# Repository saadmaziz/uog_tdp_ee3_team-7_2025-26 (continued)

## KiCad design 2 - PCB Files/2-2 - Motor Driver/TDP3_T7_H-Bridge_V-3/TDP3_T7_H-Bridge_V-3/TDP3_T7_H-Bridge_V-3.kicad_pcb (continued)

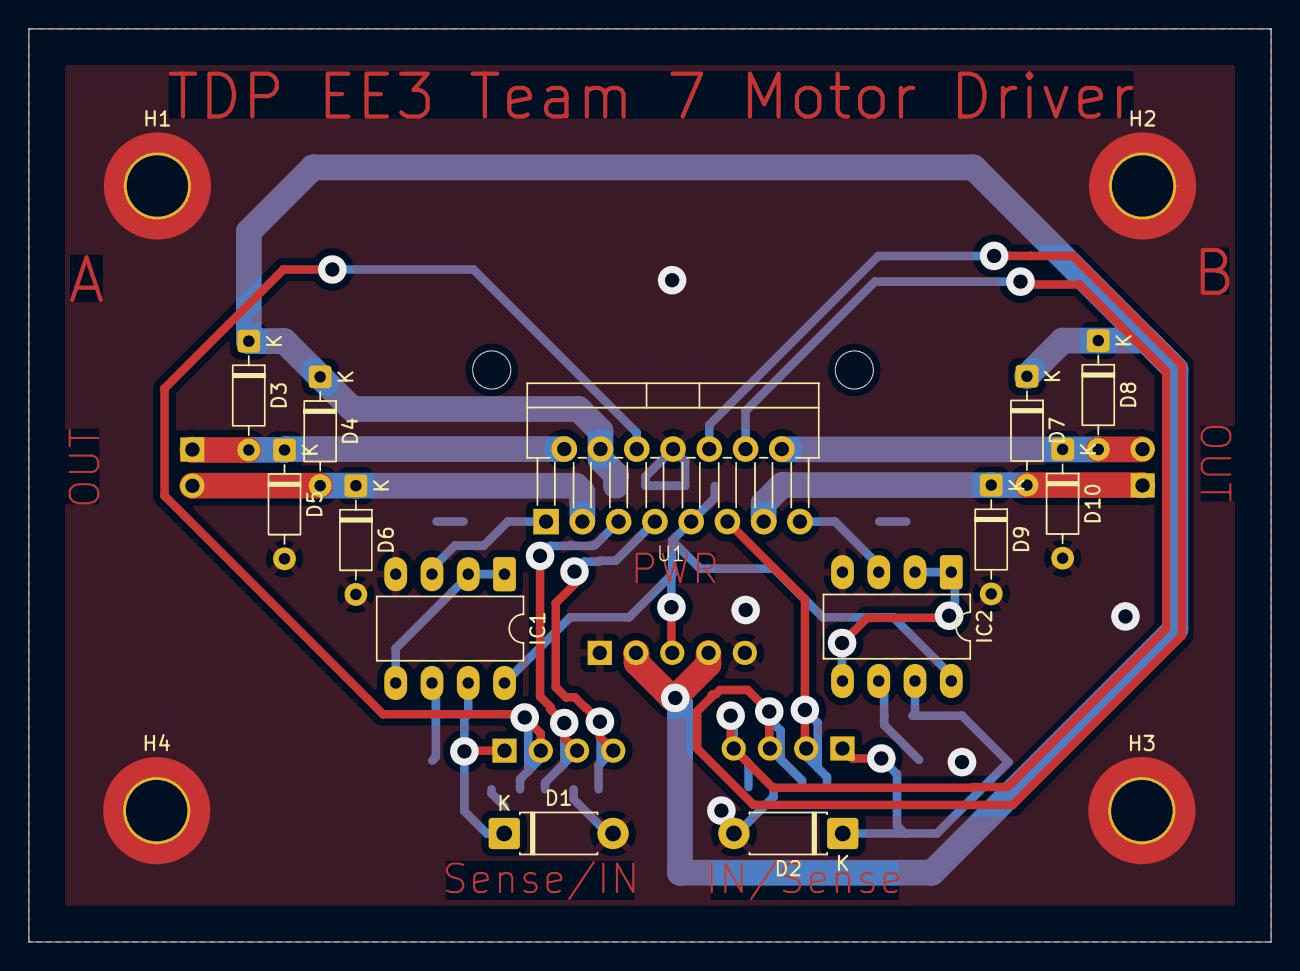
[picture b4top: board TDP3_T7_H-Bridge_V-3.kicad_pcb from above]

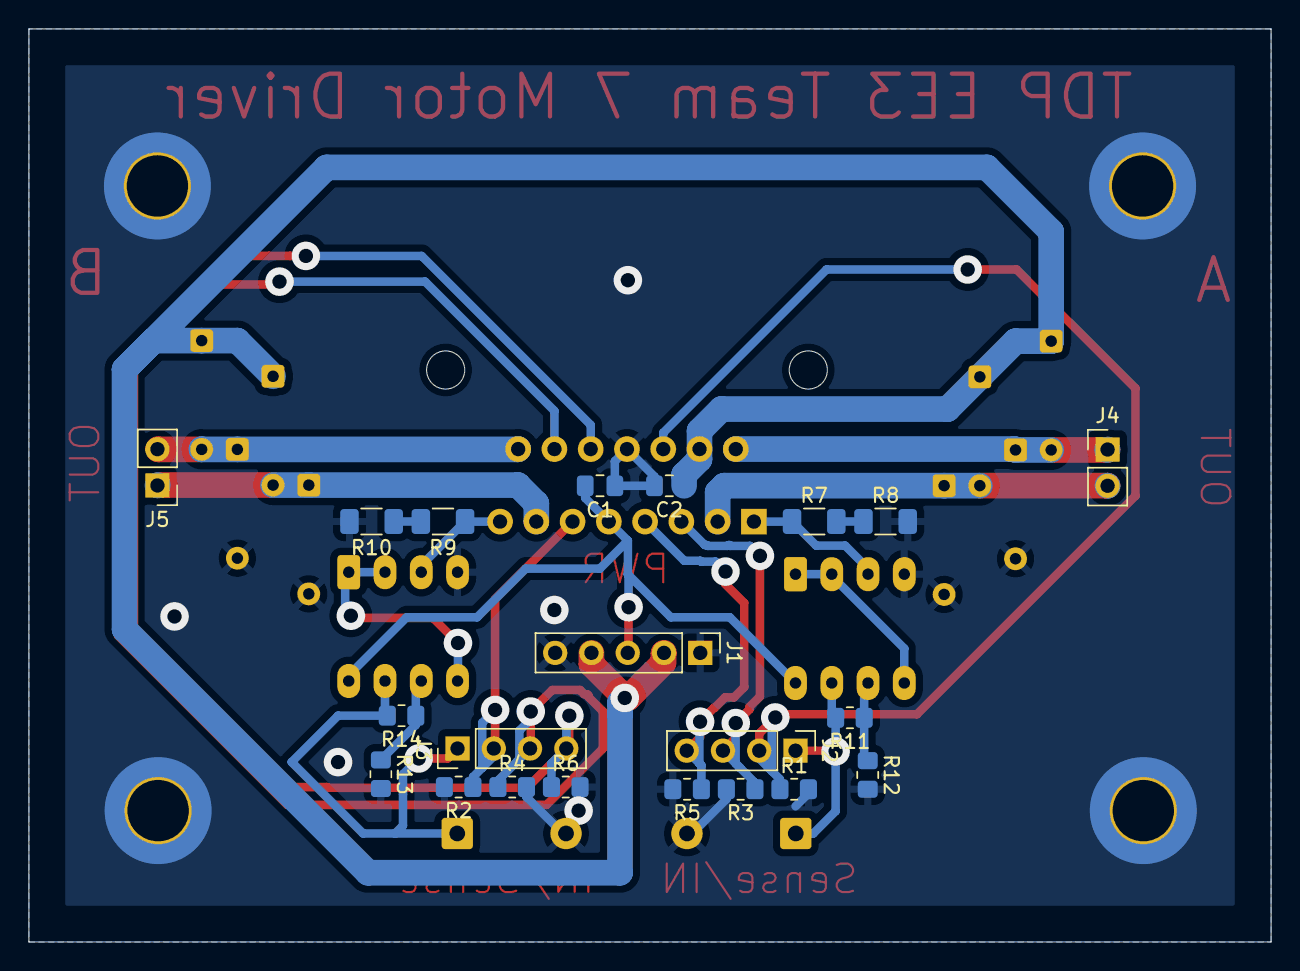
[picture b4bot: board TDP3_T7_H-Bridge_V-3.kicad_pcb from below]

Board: 2 copper layers, 87.0 x 64.0 mm, 38 parts (21 on the bottom side), 23 nets.

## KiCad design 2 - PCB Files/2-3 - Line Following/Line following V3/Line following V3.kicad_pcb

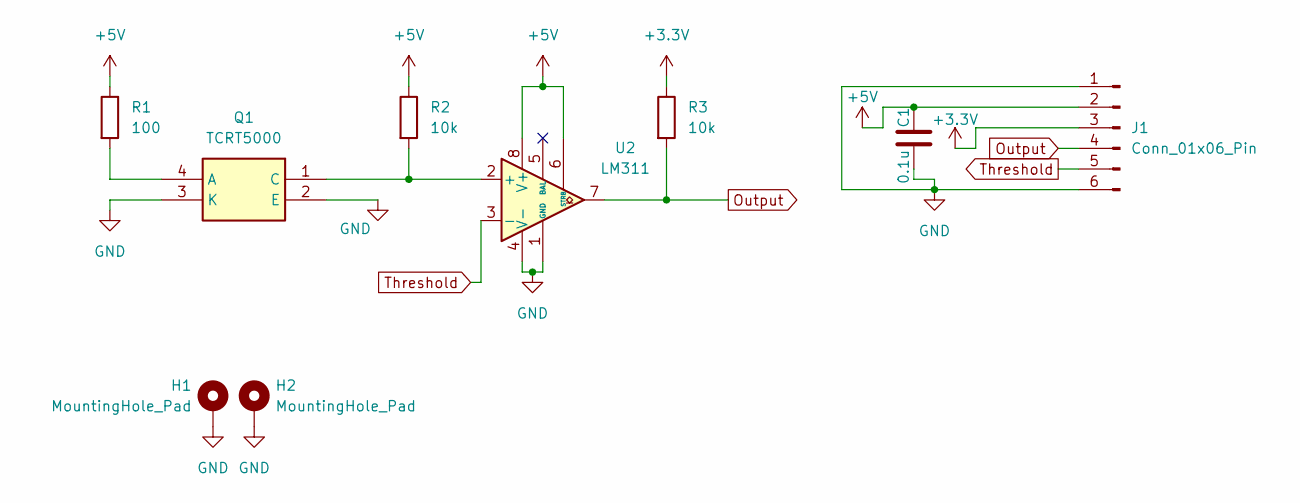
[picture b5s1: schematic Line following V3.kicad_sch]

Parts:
C1: 0.1u; C_0805_2012Metric_Pad1.18x1.45mm_HandSolder
H1, H2: MountingHole_Pad; MountingHole_3mm_Pad
J1: Conn_01x06_Pin
Q1: TCRT5000; Manufacturer_Part_Number TCRT5000
R1: 100; R_0805_2012Metric_Pad1.20x1.40mm_HandSolder
R2, R3: 10k; R_0805_2012Metric_Pad1.20x1.40mm_HandSolder
U2: LM311; DIP-8_W7.62mm_LongPads

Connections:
+3.3V: J1.3, R3.1
+5V: C1.2, J1.2, R1.1, R2.1, U2.6 (STRB), U2.8 (V+)
GND: C1.1, H1.1, H2.1, J1.1, J1.6, Q1.2 (E), Q1.3 (K), U2.1 (GND), U2.4 (V-)
unnamed: Q1.4 (A), R1.2
unnamed: Q1.1 (C), R2.2, U2.2 (+)
Output: J1.4, R3.2, U2.7
Threshold: J1.5, U2.3 (-)

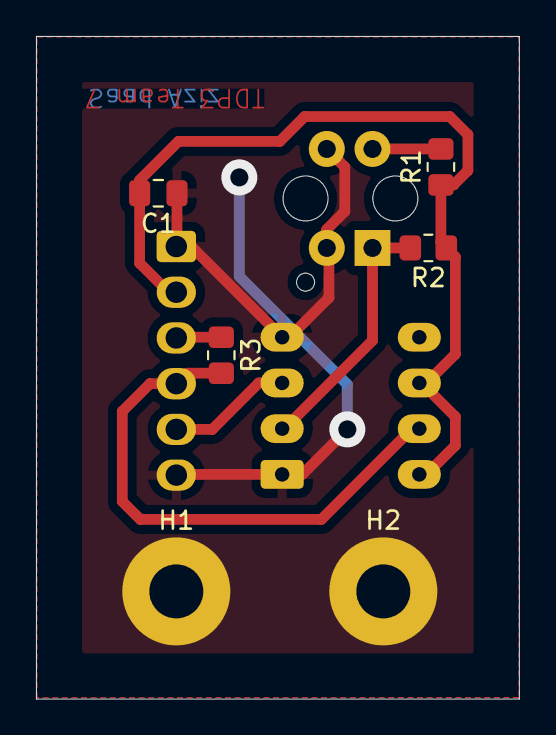
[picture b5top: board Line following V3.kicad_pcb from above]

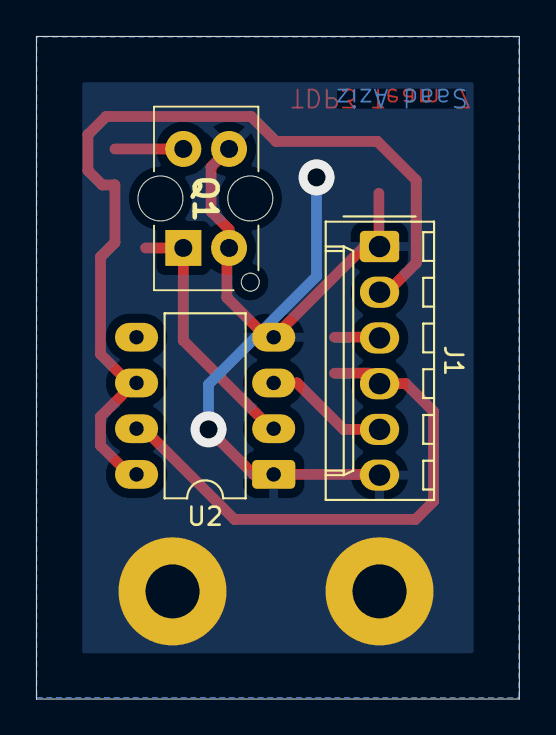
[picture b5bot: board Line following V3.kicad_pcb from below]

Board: 2 copper layers, 26.8 x 36.8 mm, 9 parts (3 on the bottom side), 7 nets.

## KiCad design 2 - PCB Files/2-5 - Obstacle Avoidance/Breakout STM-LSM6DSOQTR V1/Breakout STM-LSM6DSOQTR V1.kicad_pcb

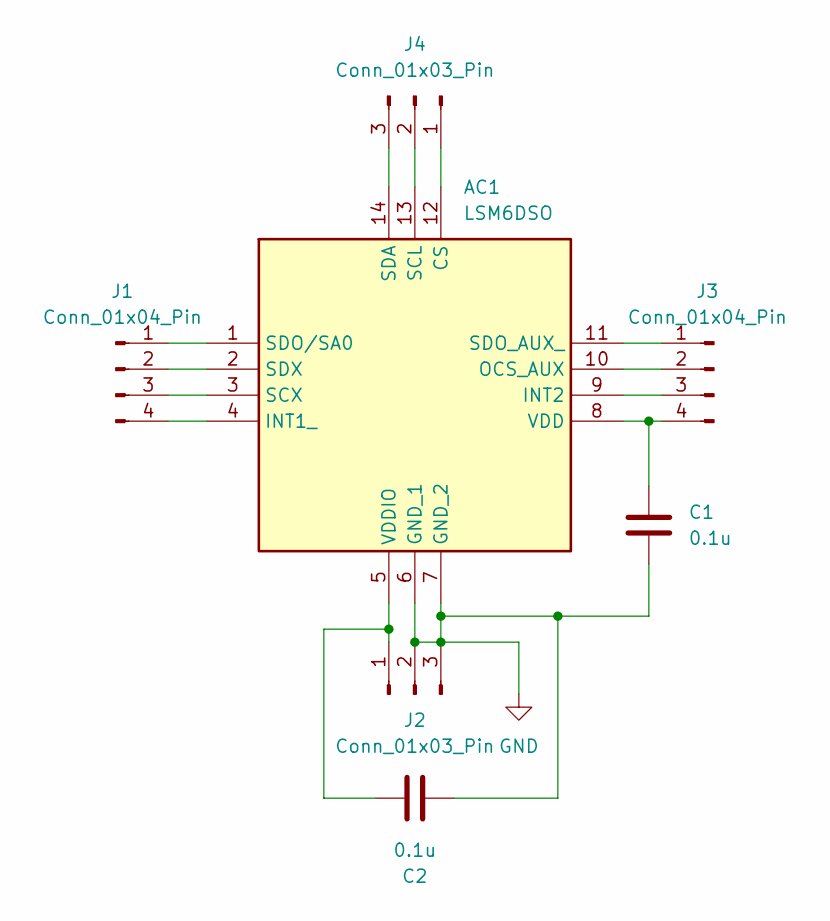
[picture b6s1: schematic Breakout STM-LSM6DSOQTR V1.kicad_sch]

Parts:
AC1: LSM6DSO; Manufacturer_Part_Number LSM6DSO; Mouser Part Number N/A
C1, C2: 0.1u; C_0603_1608Metric
J1, J3: Conn_01x04_Pin; PinHeader_1x04_P2.54mm_Vertical
J2, J4: Conn_01x03_Pin; PinHeader_1x03_P2.54mm_Vertical

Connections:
GND: AC1.6 (GND_1), AC1.7 (GND_2), C1.2, C2.1, J2.2, J2.3
unnamed: AC1.12 (CS), J4.1
unnamed: AC1.4 (INT1_), J1.4
unnamed: AC1.9 (INT2), J3.3
unnamed: AC1.10 (OCS_AUX), J3.2
unnamed: AC1.13 (SCL), J4.2
unnamed: AC1.3 (SCX), J1.3
unnamed: AC1.14 (SDA), J4.3
unnamed: AC1.11 (SDO_AUX_), J3.1
unnamed: AC1.1 (SDO/SA0), J1.1
unnamed: AC1.2 (SDX), J1.2
unnamed: AC1.8 (VDD), C1.1, J3.4
unnamed: AC1.5 (VDDIO), C2.2, J2.1

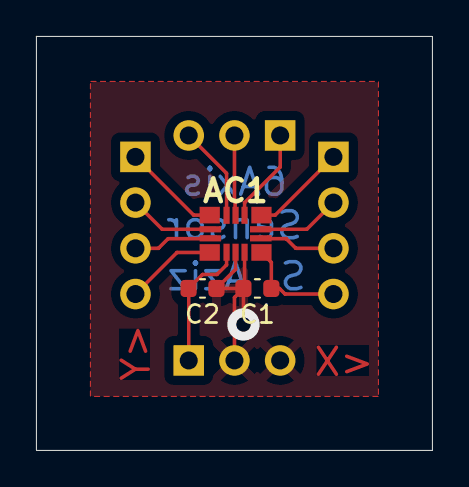
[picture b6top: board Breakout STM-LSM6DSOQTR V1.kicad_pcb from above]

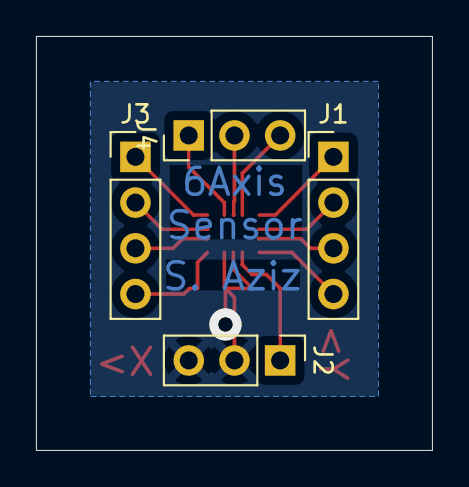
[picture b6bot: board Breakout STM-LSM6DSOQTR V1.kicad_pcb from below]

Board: 2 copper layers, 22.0 x 23.0 mm, 7 parts (4 on the bottom side), 13 nets.

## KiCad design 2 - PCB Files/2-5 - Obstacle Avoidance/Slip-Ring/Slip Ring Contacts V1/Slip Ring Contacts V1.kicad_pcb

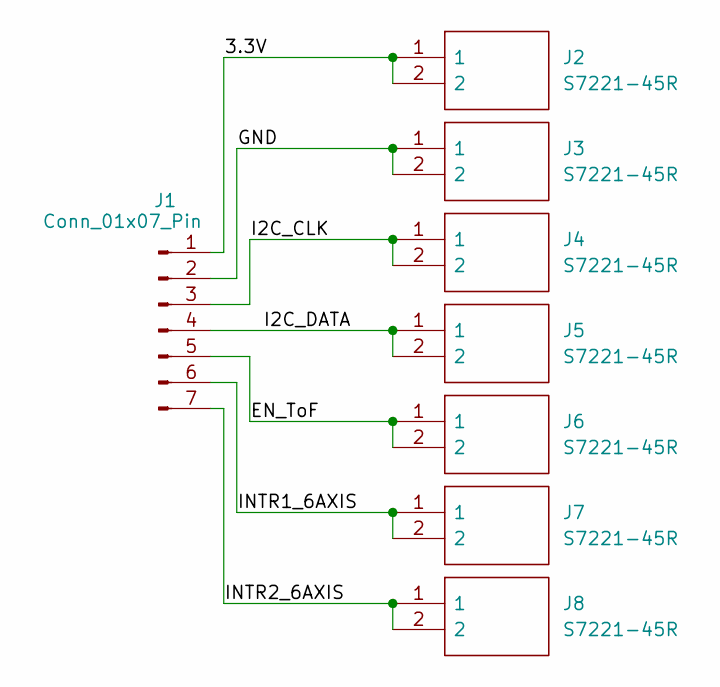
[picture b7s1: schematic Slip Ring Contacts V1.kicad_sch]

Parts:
J1: Conn_01x07_Pin; PinSocket_1x07_P2.54mm_Vertical
J2, J3, J4, J5, J6, J7, J8: S7221-45R; S722145R; Manufacturer_Part_Number S7221-45R

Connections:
/3.3V: J1.1, J2.1, J2.2
/EN_ToF: J1.5, J6.1, J6.2
/GND: J1.2, J3.1, J3.2
/I2C_CLK: J1.3, J4.1, J4.2
/I2C_DATA: J1.4, J5.1, J5.2
/INTR1_6AXIS: J1.6, J7.1, J7.2
/INTR2_6AXIS: J1.7, J8.1, J8.2

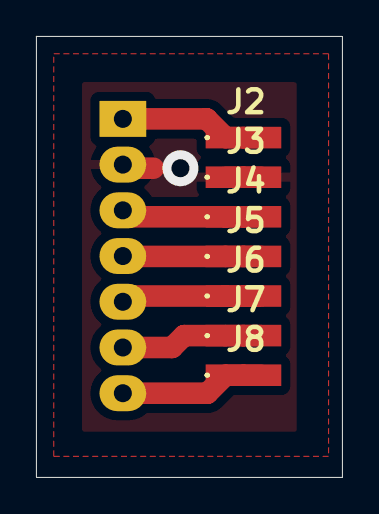
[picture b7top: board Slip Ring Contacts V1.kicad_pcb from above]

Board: 2 copper layers, 17.0 x 24.5 mm, 8 parts (1 on the bottom side), 7 nets.
